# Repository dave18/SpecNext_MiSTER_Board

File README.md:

# SpecNext_MiSTER_Board
An extension board to provide Spectrum Next functionality to MiSTER

A MiSTer hat board MiSTER based on the offical schematics to (hopefully) allow better compatibility with the Spectrum Next core, including future updates.

It adds
* SRAM - up to 2 MB as per the next using 4 x as7c34096a-10 
* VGA out (using same resistor values from Next schematic)
* Mic/Ear port
* Audio out
* Two DB9 joystick ports
* NMI/Drive/Reset buttons
* J13 header to add physical SD Card support

Core code is based on the official MiSTer Spectrum Next Core with the following changes
* Direct VGA option - will bypass MiSTer framework and send direct video signal to VGA out (note - once this option is selected the OSD will no longer be visible over VGA until option is disabled (OSD is still visible through HDMI/DVI)
* Option to set each joystick to either MiSTer input or directly from the DSub 9 inputs
* Tape loading will automatically switch between virtual tape if loaded or from the Ear port if not
* SD Card interface will use virtual cards if loaded, else will use the J13 signals (useful if you have an Active Consult drive to plug in)

Changelog

Board V1.0 (Eagle files V3a)

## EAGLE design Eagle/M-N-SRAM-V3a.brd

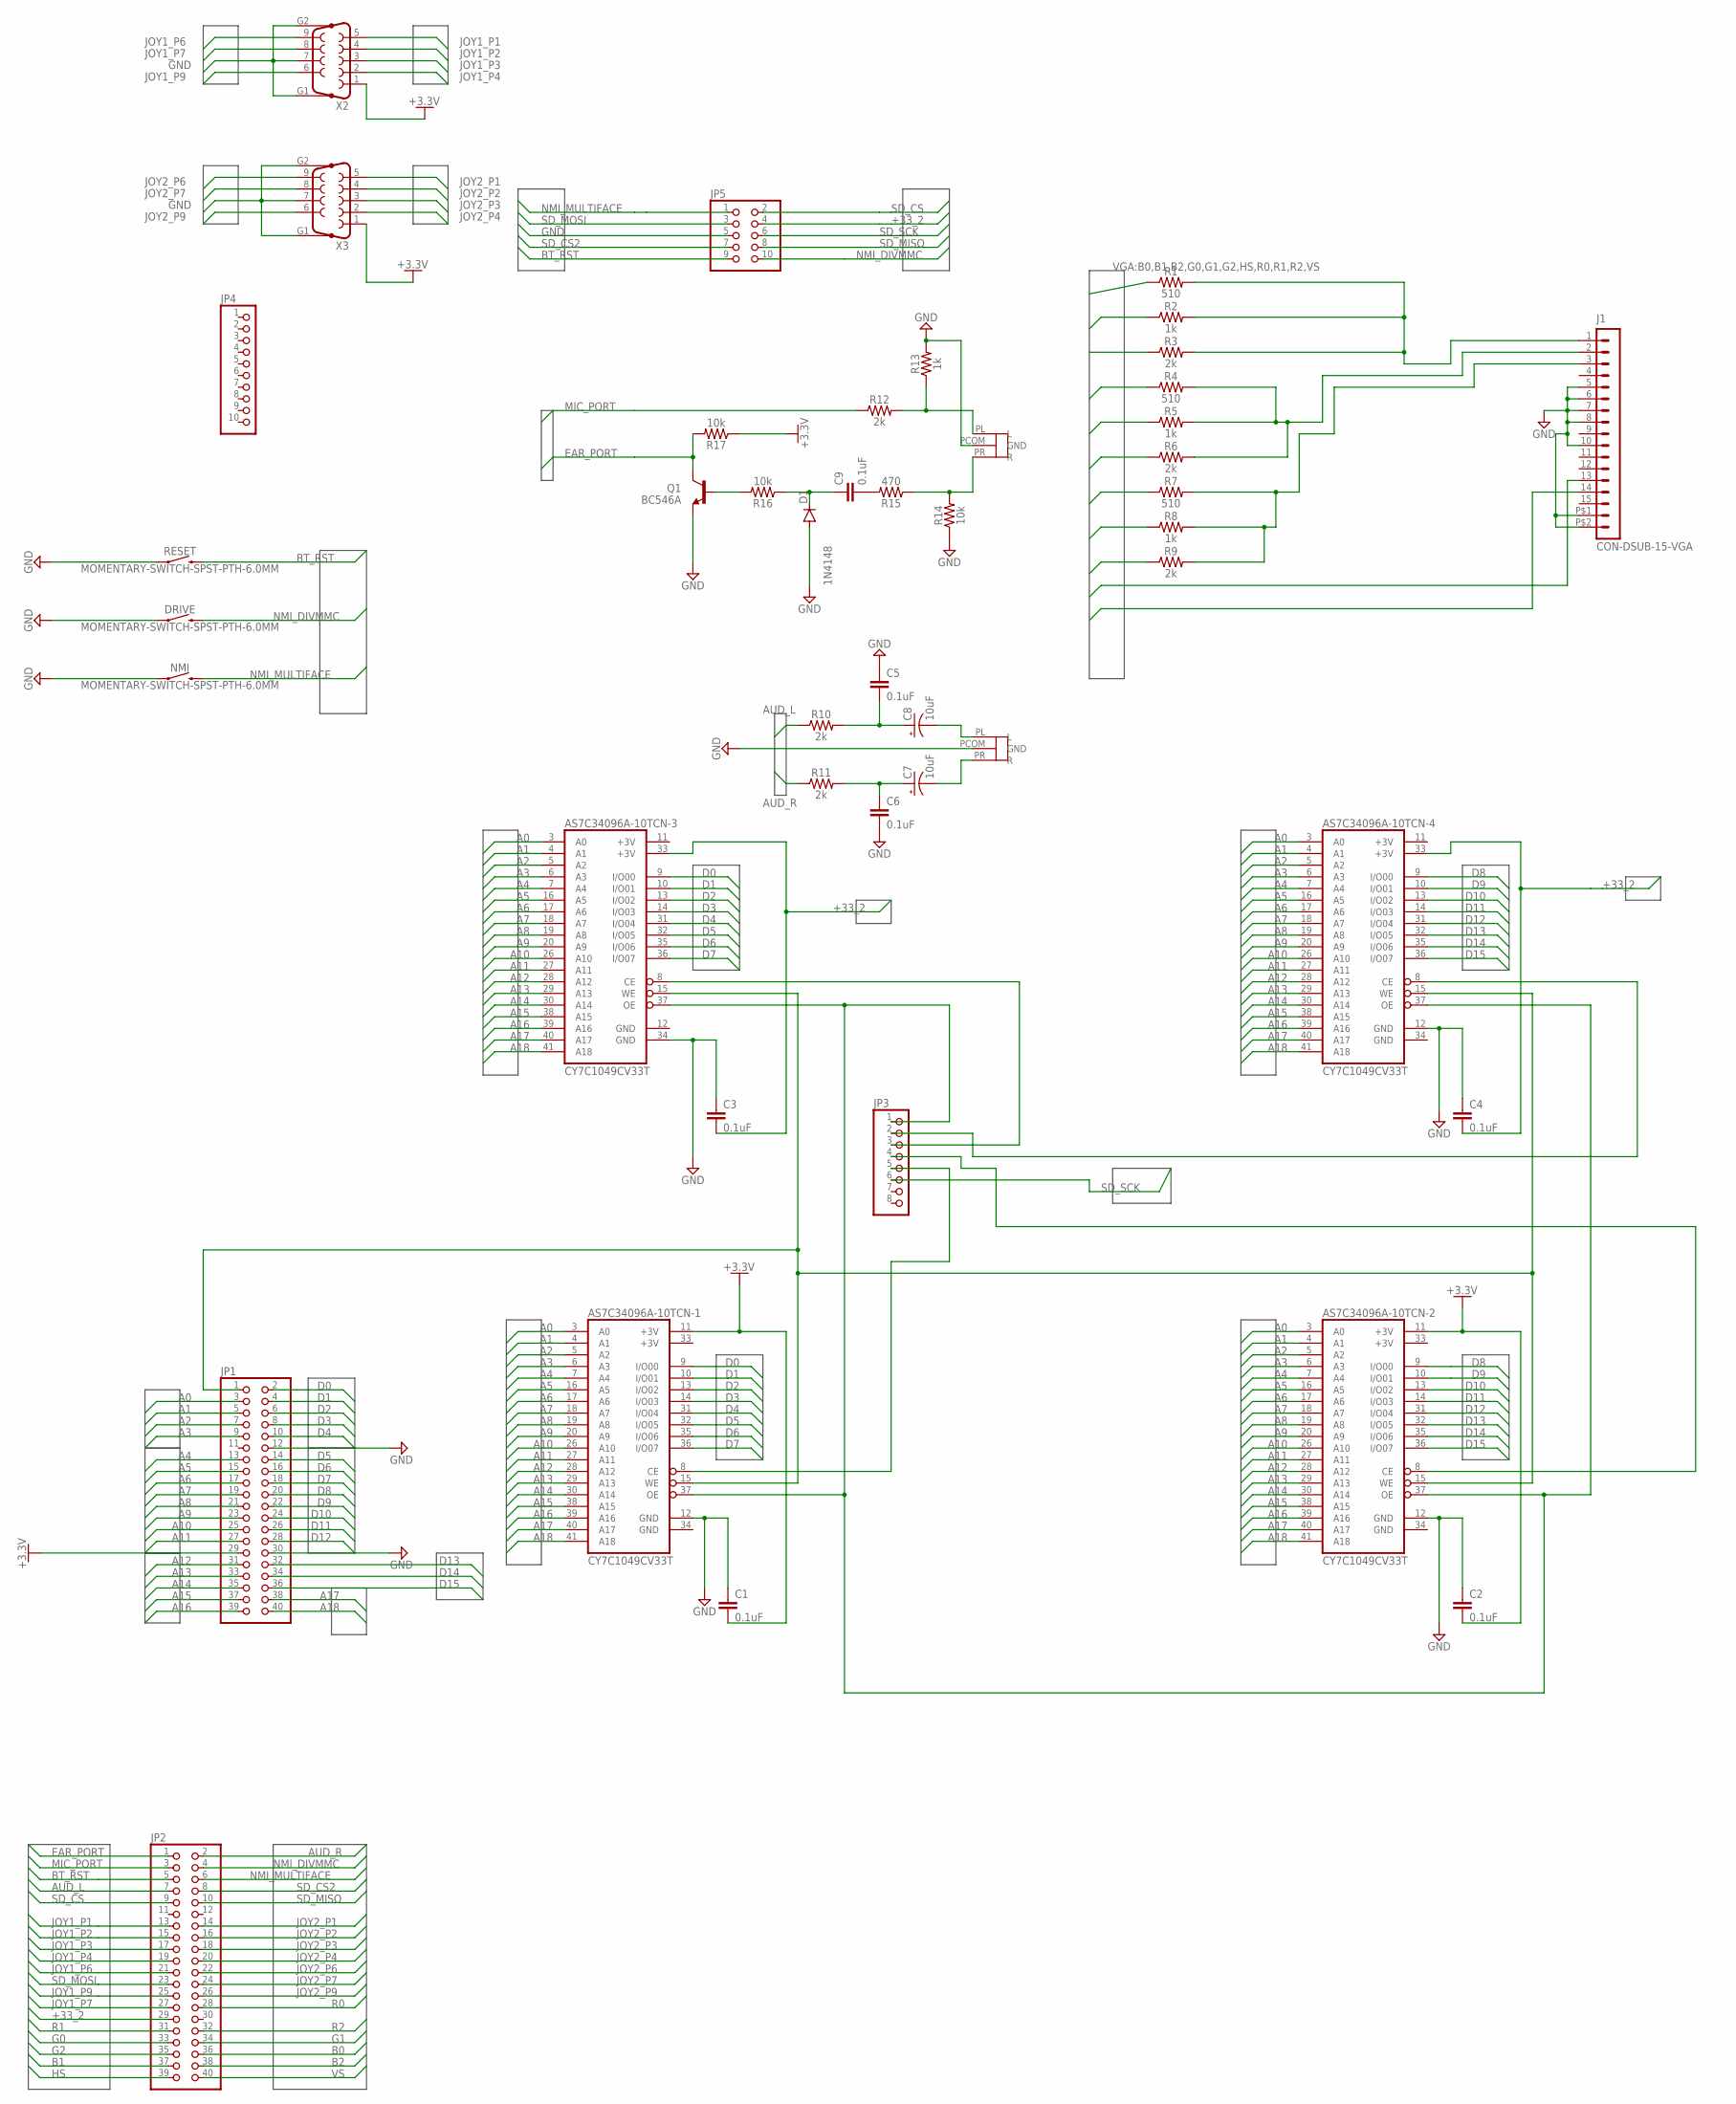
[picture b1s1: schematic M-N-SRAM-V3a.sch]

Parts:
AS7C34096A-10TCN-1, AS7C34096A-10TCN-2, AS7C34096A-10TCN-3, AS7C34096A-10TCN-4: CY7C1049CV33T; TSOPII-Z44
AUDIOOUT: AUDIOJACK
C1, C2, C3, C4, C5, C6, C9: 0.1uF; CAP-PTH-SMALL-KIT
C7, C8: 10uF; CPOL-RADIAL-2.5MM-5MM
D1: 1N4148; DO35-7
DRIVE: MOMENTARY-SWITCH-SPST-PTH-6.0MM; TACTILE_SWITCH_PTH_6.0MM
EAR/MIC: AUDIOJACK
J1: CON-DSUB-15-VGA; 181-015-212-171
JP1, JP2: PINHD-2X20; 2X20
JP3: PINHD-1X8; 1X08
JP4: PINHD-1X10; 1X10
JP5: PINHD-2X5; 2X05
NMI: MOMENTARY-SWITCH-SPST-PTH-6.0MM; TACTILE_SWITCH_PTH_6.0MM
Q1: BC546A; TO92-EBC
R1, R4, R7: 510; AXIAL-0.3
R2, R5, R8, R13: 1k; AXIAL-0.3
R3, R6, R9, R10, R11, R12: 2k; AXIAL-0.3
R14, R16, R17: 10k; AXIAL-0.3
R15: 470; AXIAL-0.3
RESET: MOMENTARY-SWITCH-SPST-PTH-6.0MM; TACTILE_SWITCH_PTH_6.0MM
X2, X3: F09HP

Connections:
+3.3V: AS7C34096A-10TCN-1.11 (+3V), AS7C34096A-10TCN-2.11 (+3V), C1.2, C2.2, R17.P$1 (1), X2.1, X3.1
+3V: AS7C34096A-10TCN-1.33 (+3V), AS7C34096A-10TCN-2.33 (+3V), AS7C34096A-10TCN-3.11 (+3V), AS7C34096A-10TCN-4.11 (+3V), JP1.29
+33_2: AS7C34096A-10TCN-3.33 (+3V), AS7C34096A-10TCN-4.33 (+3V), C3.2, C4.2, JP2.29, JP5.4
A0: AS7C34096A-10TCN-1.3 (A0), AS7C34096A-10TCN-2.3 (A0), AS7C34096A-10TCN-3.3 (A0), AS7C34096A-10TCN-4.3 (A0), JP1.3
A1: AS7C34096A-10TCN-1.4 (A1), AS7C34096A-10TCN-2.4 (A1), AS7C34096A-10TCN-3.4 (A1), AS7C34096A-10TCN-4.4 (A1), JP1.5
A2: AS7C34096A-10TCN-1.5 (A2), AS7C34096A-10TCN-2.5 (A2), AS7C34096A-10TCN-3.5 (A2), AS7C34096A-10TCN-4.5 (A2), JP1.7
A3: AS7C34096A-10TCN-1.6 (A3), AS7C34096A-10TCN-2.6 (A3), AS7C34096A-10TCN-3.6 (A3), AS7C34096A-10TCN-4.6 (A3), JP1.9
A4: AS7C34096A-10TCN-1.7 (A4), AS7C34096A-10TCN-2.7 (A4), AS7C34096A-10TCN-3.7 (A4), AS7C34096A-10TCN-4.7 (A4), JP1.13
A5: AS7C34096A-10TCN-1.16 (A5), AS7C34096A-10TCN-2.16 (A5), AS7C34096A-10TCN-3.16 (A5), AS7C34096A-10TCN-4.16 (A5), JP1.15
A6: AS7C34096A-10TCN-1.17 (A6), AS7C34096A-10TCN-2.17 (A6), AS7C34096A-10TCN-3.17 (A6), AS7C34096A-10TCN-4.17 (A6), JP1.17
A7: AS7C34096A-10TCN-1.18 (A7), AS7C34096A-10TCN-2.18 (A7), AS7C34096A-10TCN-3.18 (A7), AS7C34096A-10TCN-4.18 (A7), JP1.19
A8: AS7C34096A-10TCN-1.19 (A8), AS7C34096A-10TCN-2.19 (A8), AS7C34096A-10TCN-3.19 (A8), AS7C34096A-10TCN-4.19 (A8), JP1.21
A9: AS7C34096A-10TCN-1.20 (A9), AS7C34096A-10TCN-2.20 (A9), AS7C34096A-10TCN-3.20 (A9), AS7C34096A-10TCN-4.20 (A9), JP1.23
A10: AS7C34096A-10TCN-1.26 (A10), AS7C34096A-10TCN-2.26 (A10), AS7C34096A-10TCN-3.26 (A10), AS7C34096A-10TCN-4.26 (A10), JP1.25
A11: AS7C34096A-10TCN-1.27 (A11), AS7C34096A-10TCN-2.27 (A11), AS7C34096A-10TCN-3.27 (A11), AS7C34096A-10TCN-4.27 (A11), JP1.27
A12: AS7C34096A-10TCN-1.28 (A12), AS7C34096A-10TCN-2.28 (A12), AS7C34096A-10TCN-3.28 (A12), AS7C34096A-10TCN-4.28 (A12), JP1.31
A13: AS7C34096A-10TCN-1.29 (A13), AS7C34096A-10TCN-2.29 (A13), AS7C34096A-10TCN-3.29 (A13), AS7C34096A-10TCN-4.29 (A13), JP1.33
A14: AS7C34096A-10TCN-1.30 (A14), AS7C34096A-10TCN-2.30 (A14), AS7C34096A-10TCN-3.30 (A14), AS7C34096A-10TCN-4.30 (A14), JP1.35
A15: AS7C34096A-10TCN-1.38 (A15), AS7C34096A-10TCN-2.38 (A15), AS7C34096A-10TCN-3.38 (A15), AS7C34096A-10TCN-4.38 (A15), JP1.37
A16: AS7C34096A-10TCN-1.39 (A16), AS7C34096A-10TCN-2.39 (A16), AS7C34096A-10TCN-3.39 (A16), AS7C34096A-10TCN-4.39 (A16), JP1.39
A17: AS7C34096A-10TCN-1.40 (A17), AS7C34096A-10TCN-2.40 (A17), AS7C34096A-10TCN-3.40 (A17), AS7C34096A-10TCN-4.40 (A17), JP1.38
A18: AS7C34096A-10TCN-1.41 (A18), AS7C34096A-10TCN-2.41 (A18), AS7C34096A-10TCN-3.41 (A18), AS7C34096A-10TCN-4.41 (A18), JP1.40
AUDIO_OUT_L: AUDIOOUT.PL (L), C8.2 (-)
AUDIO_OUT_L1: C5.2, C8.1 (+), R10.P$2 (2)
AUDIO_OUT_R: AUDIOOUT.PR (R), C7.2 (-)
AUDIO_OUT_R1: C6.1, C7.1 (+), R11.P$2 (2)
AUD_L: JP2.7, R10.P$1 (1)
AUD_R: JP2.2, R11.P$1 (1)
B0: JP2.36, R7.P$1 (1)
B1: JP2.37, R8.P$1 (1)
B2: JP2.38, R9.P$1 (1)
BT_RST: JP2.5, JP5.9, RESET.3 (2)
D0: AS7C34096A-10TCN-1.9 (I/O00), AS7C34096A-10TCN-3.9 (I/O00), JP1.2
D1: AS7C34096A-10TCN-1.10 (I/O01), AS7C34096A-10TCN-3.10 (I/O01), JP1.4
D2: AS7C34096A-10TCN-1.13 (I/O02), AS7C34096A-10TCN-3.13 (I/O02), JP1.6
D3: AS7C34096A-10TCN-1.14 (I/O03), AS7C34096A-10TCN-3.14 (I/O03), JP1.8
D4: AS7C34096A-10TCN-1.31 (I/O04), AS7C34096A-10TCN-3.31 (I/O04), JP1.10
D5: AS7C34096A-10TCN-1.32 (I/O05), AS7C34096A-10TCN-3.32 (I/O05), JP1.14
D6: AS7C34096A-10TCN-1.35 (I/O06), AS7C34096A-10TCN-3.35 (I/O06), JP1.16
D7: AS7C34096A-10TCN-1.36 (I/O07), AS7C34096A-10TCN-3.36 (I/O07), JP1.18
D8: AS7C34096A-10TCN-2.9 (I/O00), AS7C34096A-10TCN-4.9 (I/O00), JP1.20
D9: AS7C34096A-10TCN-2.10 (I/O01), AS7C34096A-10TCN-4.10 (I/O01), JP1.22
D10: AS7C34096A-10TCN-2.13 (I/O02), AS7C34096A-10TCN-4.13 (I/O02), JP1.24
D11: AS7C34096A-10TCN-2.14 (I/O03), AS7C34096A-10TCN-4.14 (I/O03), JP1.26
D12: AS7C34096A-10TCN-2.31 (I/O04), AS7C34096A-10TCN-4.31 (I/O04), JP1.28
D13: AS7C34096A-10TCN-2.32 (I/O05), AS7C34096A-10TCN-4.32 (I/O05), JP1.32
D14: AS7C34096A-10TCN-2.35 (I/O06), AS7C34096A-10TCN-4.35 (I/O06), JP1.34
D15: AS7C34096A-10TCN-2.36 (I/O07), AS7C34096A-10TCN-4.36 (I/O07), JP1.36
EAR_PORT: JP2.1, Q1.C, R17.P$2 (2)
G0: JP2.33, R4.P$1 (1)
G1: JP2.34, R5.P$1 (1)
G2: JP2.35, R6.P$1 (1)
GND: AS7C34096A-10TCN-1.12 (GND), AS7C34096A-10TCN-1.34 (GND), AS7C34096A-10TCN-2.12 (GND), AS7C34096A-10TCN-2.34 (GND), AS7C34096A-10TCN-3.12 (GND), AS7C34096A-10TCN-3.34 (GND), AS7C34096A-10TCN-4.12 (GND), AS7C34096A-10TCN-4.34 (GND), AUDIOOUT.PCOM (GND), C1.1, C2.1, C3.1, C4.1, C5.1, C6.2, D1.A, DRIVE.1, EAR/MIC.PCOM (GND), J1.5, J1.6, J1.7, J1.8, J1.10, J1.P$1 (16), J1.P$2 (17), JP1.12, JP1.30, JP5.5, NMI.1, Q1.E, R13.P$2 (2), R14.P$1 (1), RESET.1, X2.7, X2.G1, X2.G2, X3.7, X3.G1, X3.G2
HS: J1.13, JP2.39
JOY1_P1: JP2.13, X2.5
JOY1_P2: JP2.15, X2.4
JOY1_P3: JP2.17, X2.3
JOY1_P4: JP2.19, X2.2
JOY1_P6: JP2.21, X2.9
JOY1_P7: JP2.27, X2.8
JOY1_P9: JP2.25, X2.6
JOY2_P1: JP2.14, X3.5
JOY2_P2: JP2.16, X3.4
JOY2_P3: JP2.18, X3.3
JOY2_P4: JP2.20, X3.2
JOY2_P6: JP2.22, X3.9
JOY2_P7: JP2.24, X3.8
JOY2_P9: JP2.26, X3.6
MIC_PORT: JP2.3, R12.P$1 (1)
unnamed: EAR/MIC.PL (L), R12.P$2 (2), R13.P$1 (1)
unnamed: C9.2, R15.P$2 (2)
unnamed: EAR/MIC.PR (R), R14.P$2 (2), R15.P$1 (1)
unnamed: C9.1, D1.C, R16.P$1 (1)
unnamed: Q1.B, R16.P$2 (2)
NMI_DIVMMC: DRIVE.3 (2), JP2.4, JP5.10
NMI_MULTIFACE: JP2.6, JP5.1, NMI.3 (2)
R0: JP2.28, R1.P$1 (1)
R1: JP2.31, R2.P$1 (1)
R2: JP2.32, R3.P$1 (1)
RAM_CE1: AS7C34096A-10TCN-1.8 (CE), JP3.5
RAM_CE2: AS7C34096A-10TCN-2.8 (CE), JP3.4
RAM_CE3: AS7C34096A-10TCN-3.8 (CE), JP3.3
RAM_CE4: AS7C34096A-10TCN-4.8 (CE), JP3.2
RAM_OE: AS7C34096A-10TCN-1.37 (OE), AS7C34096A-10TCN-2.37 (OE), AS7C34096A-10TCN-3.37 (OE), AS7C34096A-10TCN-4.37 (OE), JP3.1
RAM_WE: AS7C34096A-10TCN-1.15 (WE), AS7C34096A-10TCN-2.15 (WE), AS7C34096A-10TCN-3.15 (WE), AS7C34096A-10TCN-4.15 (WE), JP1.1
SD_CS: JP2.9, JP5.2
SD_CS2: JP2.8, JP5.7
SD_MISO: JP2.10, JP5.8
SD_MOSI: JP2.23, JP5.3
SD_SCK: JP3.6, JP5.6
VGA_BLUE: J1.3, R7.P$2 (2), R8.P$2 (2), R9.P$2 (2)
VGA_GREEN: J1.2, R4.P$2 (2), R5.P$2 (2), R6.P$2 (2)
VGA_RED: J1.1, R1.P$2 (2), R2.P$2 (2), R3.P$2 (2)
VS: J1.14, JP2.40

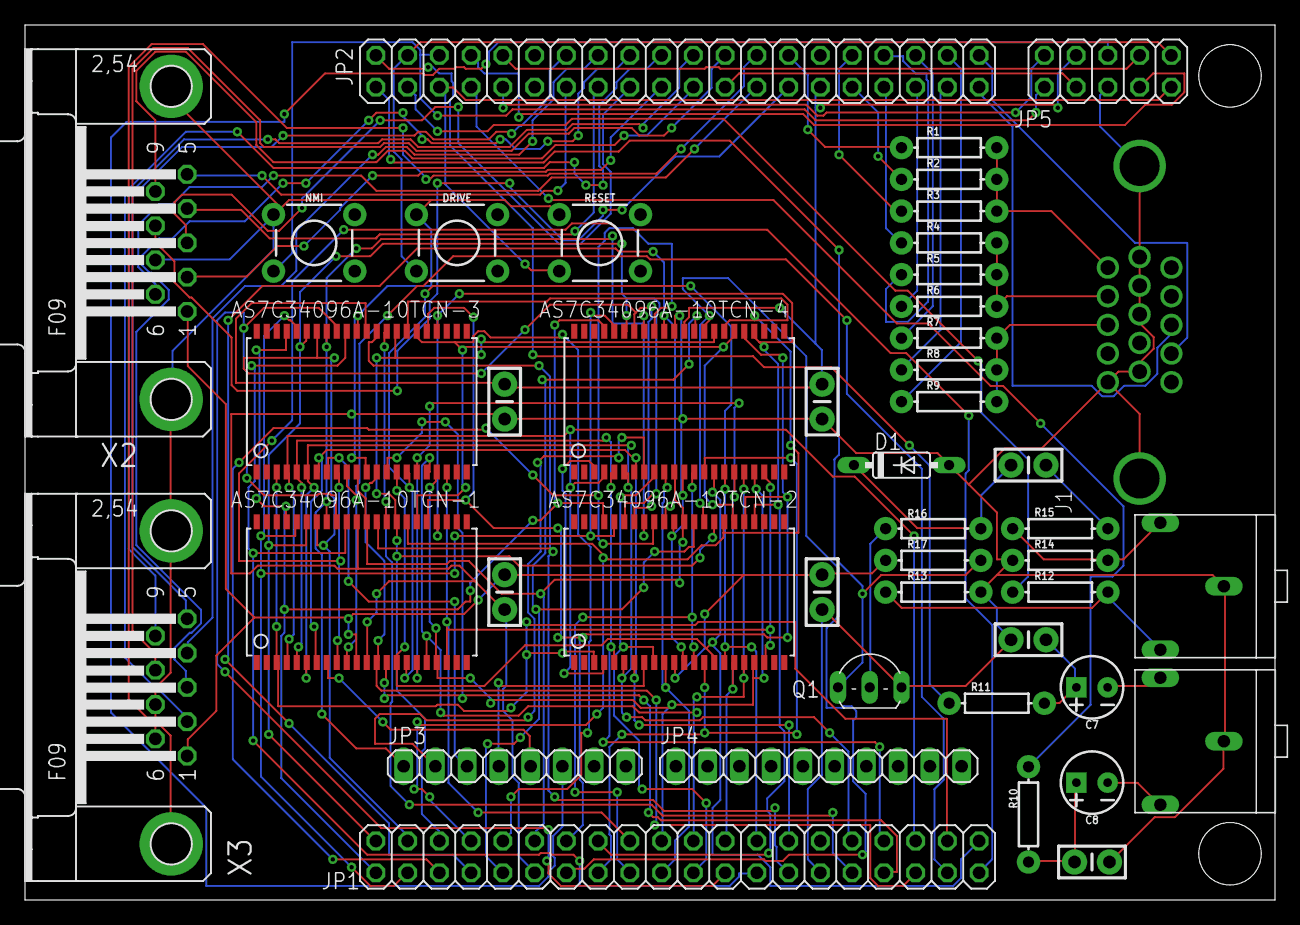
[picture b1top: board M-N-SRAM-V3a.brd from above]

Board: 2 copper layers, 100.0 x 70.0 mm, 45 parts (0 on the bottom side), 94 nets.

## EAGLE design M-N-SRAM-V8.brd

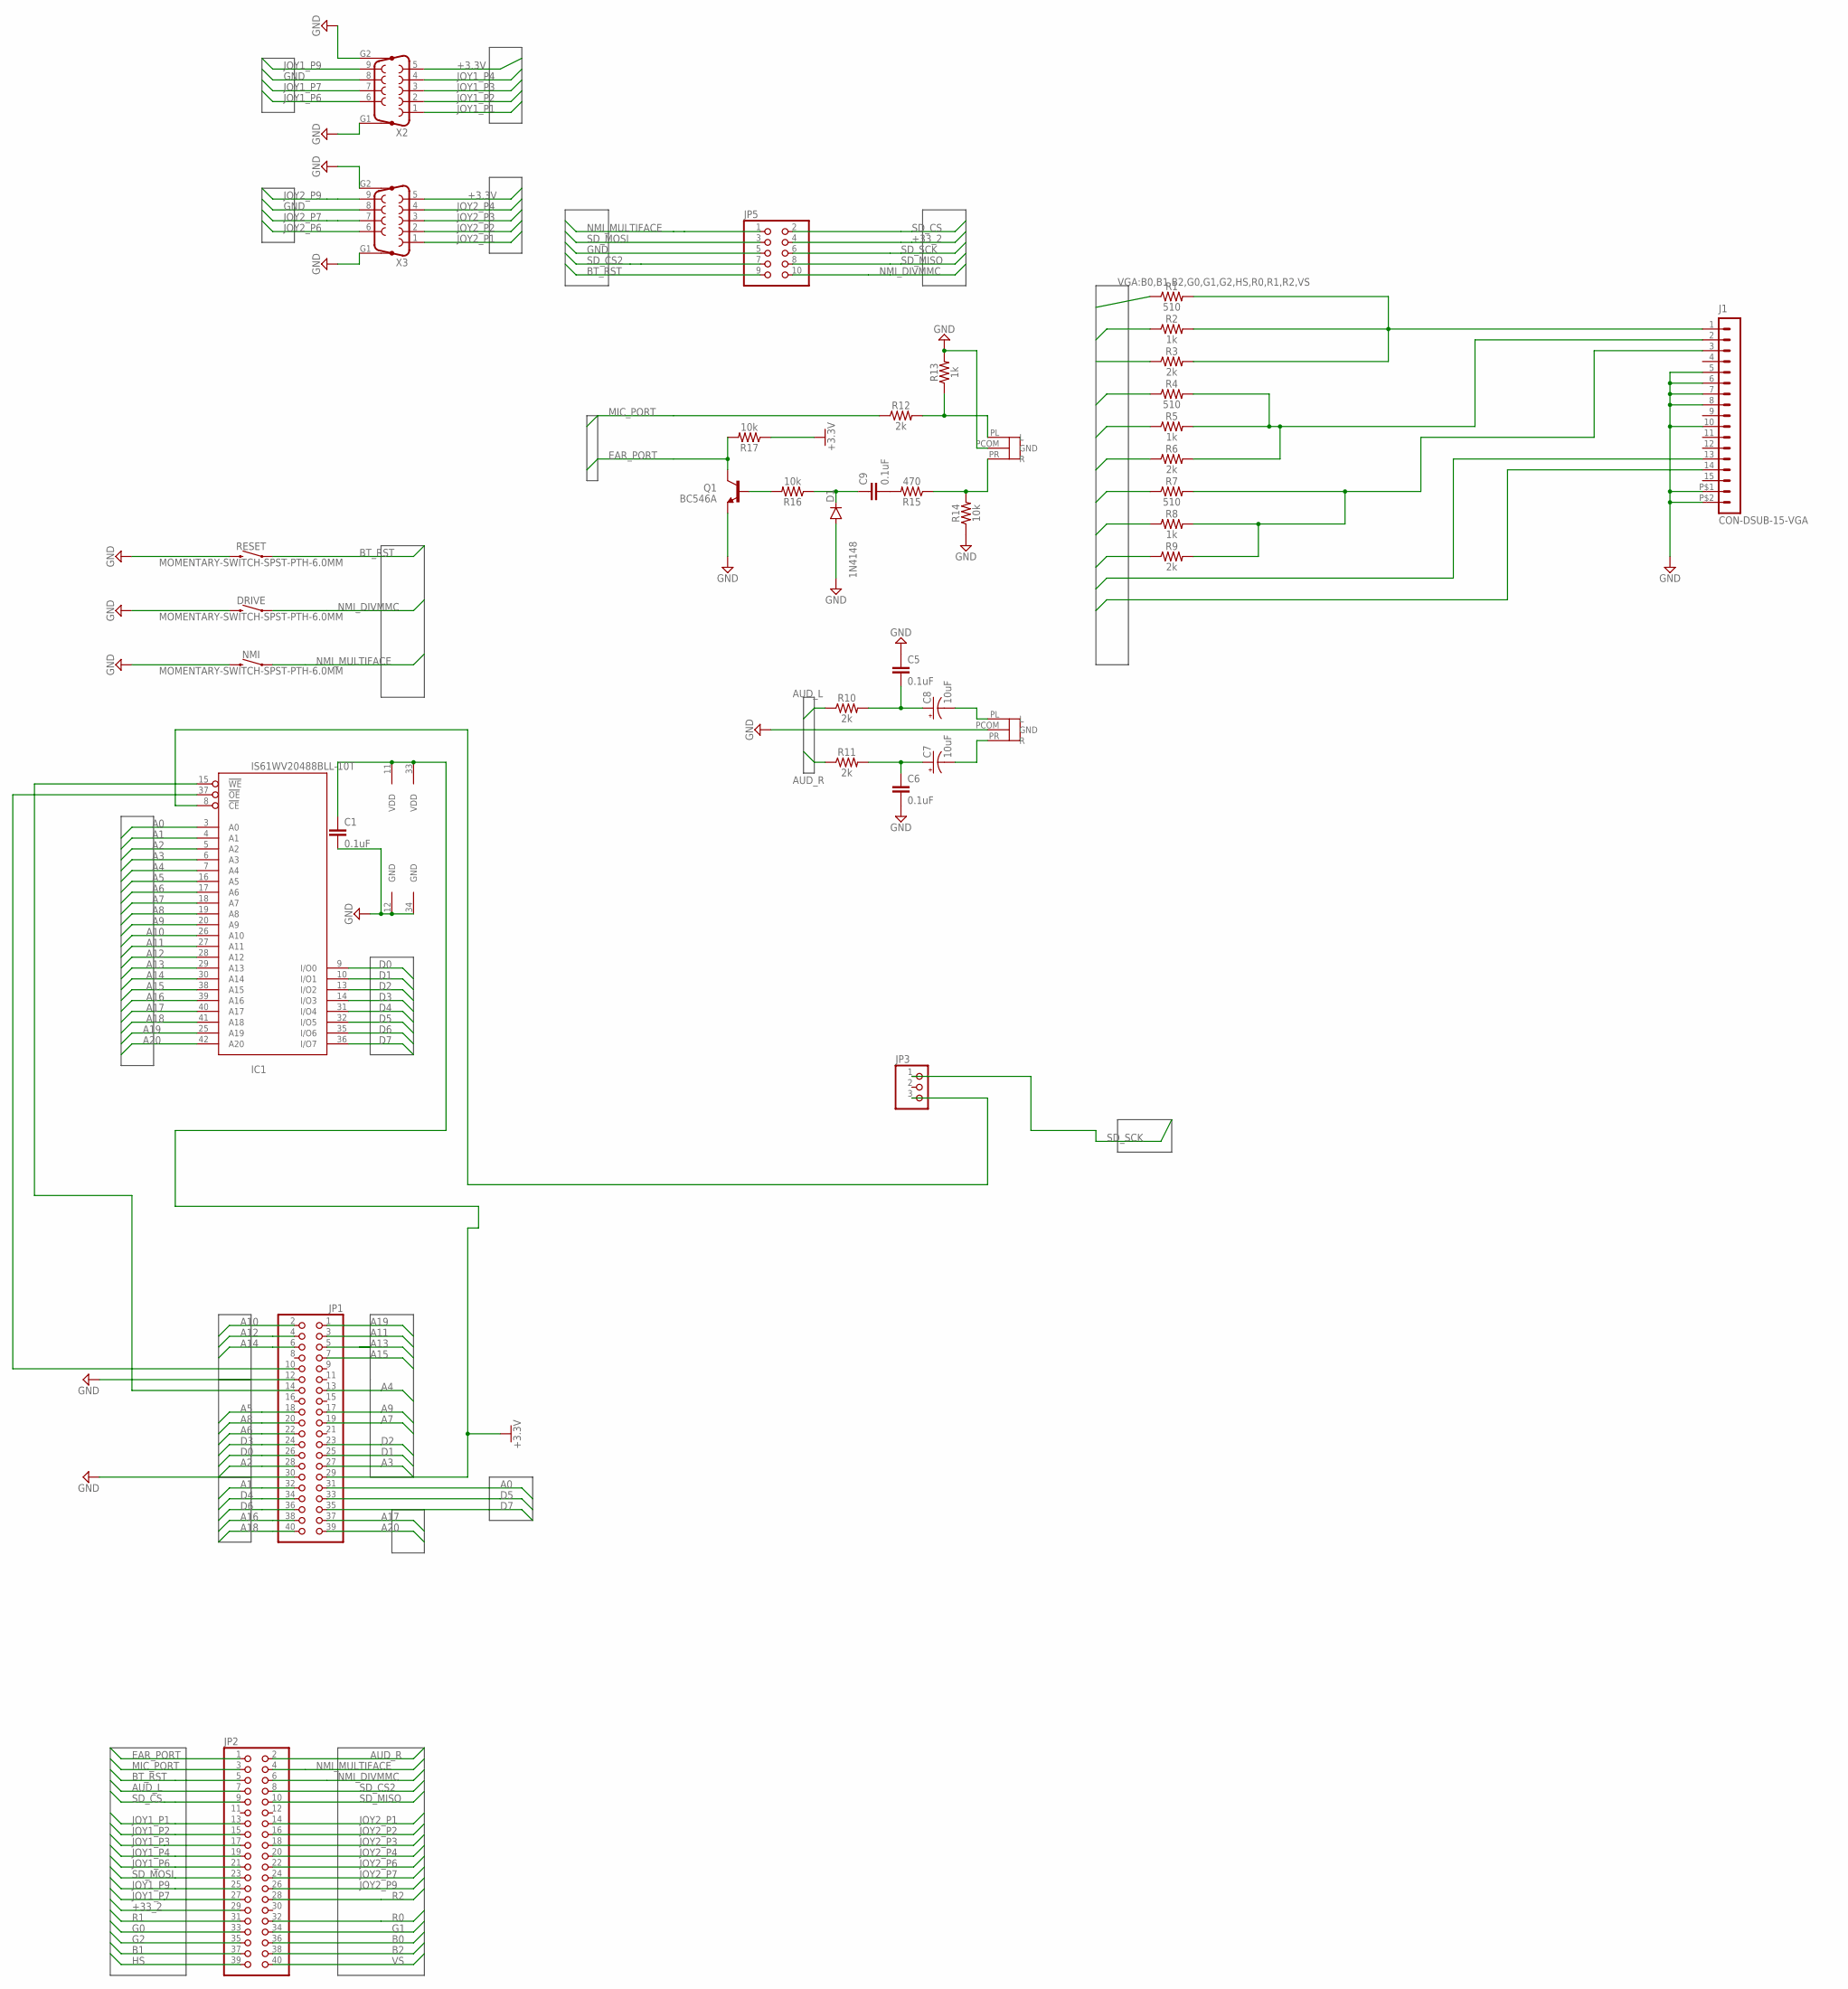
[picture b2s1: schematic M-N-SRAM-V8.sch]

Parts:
AUDIOOUT: AUDIOJACK
C1, C5, C6, C9: 0.1uF; CAP-PTH-SMALL-KIT
C7, C8: 10uF; CPOL-RADIAL-2.5MM-5MM
D1: 1N4148; DO35-7
DRIVE: MOMENTARY-SWITCH-SPST-PTH-6.0MM; TACTILE_SWITCH_PTH_6.0MM
EAR/MIC: AUDIOJACK
IC1: IS61WV20488BLL-10T; TSOP-II-44
J1: CON-DSUB-15-VGA; 181-015-212-171
JP1, JP2: PINHD-2X20; 2X20
JP3: PINHD-1X3; 1X03
JP5: PINHD-2X5; 2X05
NMI: MOMENTARY-SWITCH-SPST-PTH-6.0MM; TACTILE_SWITCH_PTH_6.0MM
Q1: BC546A; TO92-EBC
R1, R4, R7: 510; AXIAL-0.3
R2, R5, R8, R13: 1k; AXIAL-0.3
R3, R6, R9, R10, R11, R12: 2k; AXIAL-0.3
R14, R16, R17: 10k; AXIAL-0.3
R15: 470; AXIAL-0.3
RESET: MOMENTARY-SWITCH-SPST-PTH-6.0MM; TACTILE_SWITCH_PTH_6.0MM
X2, X3: F09HP

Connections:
+3.3V: C1.1, IC1.11 (VDD), IC1.33 (VDD), JP1.29, R17.P$1 (1), X2.5, X3.5
+33_2: JP2.29, JP5.4
A0: IC1.3 (A0), JP1.31
A1: IC1.4 (A1), JP1.32
A2: IC1.5 (A2), JP1.28
A3: IC1.6 (A3), JP1.27
A4: IC1.7 (A4), JP1.13
A5: IC1.16 (A5), JP1.18
A6: IC1.17 (A6), JP1.22
A7: IC1.18 (A7), JP1.19
A8: IC1.19 (A8), JP1.20
A9: IC1.20 (A9), JP1.17
A10: IC1.26 (A10), JP1.2
A11: IC1.27 (A11), JP1.3
A12: IC1.28 (A12), JP1.4
A13: IC1.29 (A13), JP1.5
A14: IC1.30 (A14), JP1.6
A15: IC1.38 (A15), JP1.7
A16: IC1.39 (A16), JP1.38
A17: IC1.40 (A17), JP1.37
A18: IC1.41 (A18), JP1.40
A19: IC1.25 (A19), JP1.1
A20: IC1.42 (A20), JP1.39
AUDIO_OUT_L: AUDIOOUT.PL (L), C8.2 (-)
AUDIO_OUT_L1: C5.2, C8.1 (+), R10.P$2 (2)
AUDIO_OUT_R: AUDIOOUT.PR (R), C7.2 (-)
AUDIO_OUT_R1: C6.1, C7.1 (+), R11.P$2 (2)
AUD_L: JP2.7, R10.P$1 (1)
AUD_R: JP2.2, R11.P$1 (1)
B0: JP2.36, R7.P$1 (1)
B1: JP2.37, R8.P$1 (1)
B2: JP2.38, R9.P$1 (1)
BT_RST: JP2.5, JP5.9, RESET.1
D0: IC1.9 (I/O0), JP1.26
D1: IC1.10 (I/O1), JP1.25
D2: IC1.13 (I/O2), JP1.23
D3: IC1.14 (I/O3), JP1.24
D4: IC1.31 (I/O4), JP1.34
D5: IC1.32 (I/O5), JP1.33
D6: IC1.35 (I/O6), JP1.36
D7: IC1.36 (I/O7), JP1.35
EAR_PORT: JP2.1, Q1.C, R17.P$2 (2)
G0: JP2.33, R4.P$1 (1)
G1: JP2.34, R5.P$1 (1)
G2: JP2.35, R6.P$1 (1)
GND: AUDIOOUT.PCOM (GND), C1.2, C5.1, C6.2, D1.A, DRIVE.3 (2), EAR/MIC.PCOM (GND), IC1.12 (GND), IC1.34 (GND), J1.5, J1.6, J1.7, J1.8, J1.10, J1.P$1 (16), J1.P$2 (17), JP1.12, JP1.30, JP5.5, NMI.3 (2), Q1.E, R13.P$2 (2), R14.P$1 (1), RESET.3 (2), X2.8, X2.G1, X2.G2, X3.8, X3.G1, X3.G2
HS: J1.13, JP2.39
JOY1_P1: JP2.13, X2.1
JOY1_P2: JP2.15, X2.2
JOY1_P3: JP2.17, X2.3
JOY1_P4: JP2.19, X2.4
JOY1_P6: JP2.21, X2.6
JOY1_P7: JP2.27, X2.7
JOY1_P9: JP2.25, X2.9
JOY2_P1: JP2.14, X3.1
JOY2_P2: JP2.16, X3.2
JOY2_P3: JP2.18, X3.3
JOY2_P4: JP2.20, X3.4
JOY2_P6: JP2.22, X3.6
JOY2_P7: JP2.24, X3.7
JOY2_P9: JP2.26, X3.9
MIC_PORT: JP2.3, R12.P$1 (1)
unnamed: EAR/MIC.PL (L), R12.P$2 (2), R13.P$1 (1)
unnamed: C9.2, R15.P$2 (2)
unnamed: EAR/MIC.PR (R), R14.P$2 (2), R15.P$1 (1)
unnamed: C9.1, D1.C, R16.P$1 (1)
unnamed: Q1.B, R16.P$2 (2)
NMI_DIVMMC: DRIVE.1, JP2.6, JP5.10
NMI_MULTIFACE: JP2.4, JP5.1, NMI.1
R0: JP2.32, R1.P$1 (1)
R1: JP2.31, R2.P$1 (1)
R2: JP2.28, R3.P$1 (1)
RAM_CE: IC1.8 (!CE), JP3.3
RAM_OE: IC1.37 (!OE), JP1.10
RAM_WE: IC1.15 (!WE), JP1.14
SD_CS: JP2.9, JP5.2
SD_CS2: JP2.8, JP5.7
SD_MISO: JP2.10, JP5.8
SD_MOSI: JP2.23, JP5.3
SD_SCK: JP3.1, JP5.6
VGA_BLUE: J1.3, R7.P$2 (2), R8.P$2 (2), R9.P$2 (2)
VGA_GREEN: J1.2, R4.P$2 (2), R5.P$2 (2), R6.P$2 (2)
VGA_RED: J1.1, R1.P$2 (2), R2.P$2 (2), R3.P$2 (2)
VS: J1.14, JP2.40

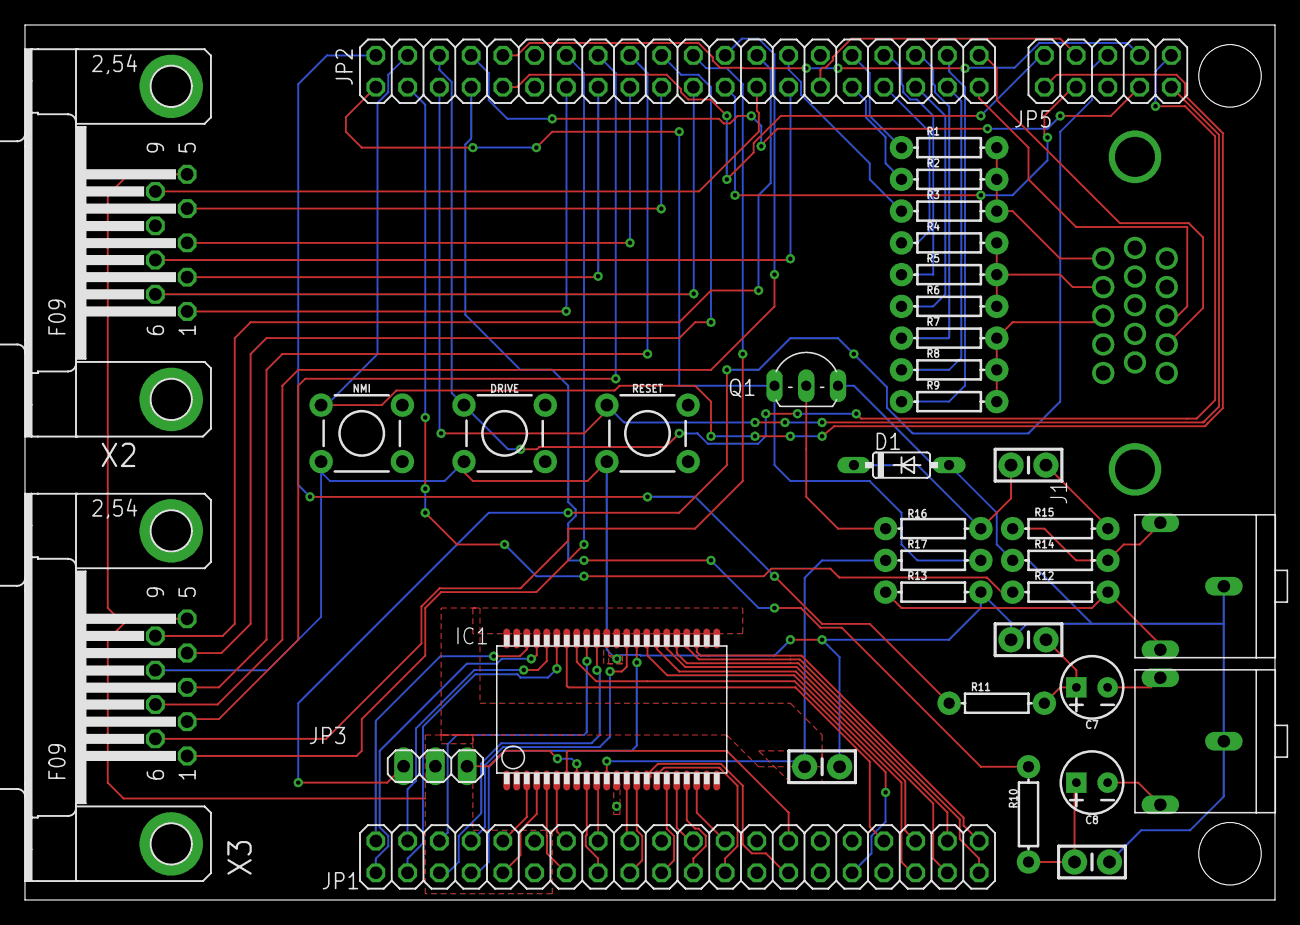
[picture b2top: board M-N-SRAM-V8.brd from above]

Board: 2 copper layers, 100.0 x 70.0 mm, 38 parts (0 on the bottom side), 84 nets.

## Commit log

2021-03-24 Rename images
2021-03-24 Add v8 Eagle files
    V8 Eagle files relate to official V2.0 board
2021-03-24 Schematic Correction
2022-01-31 Add files via upload
    Upload of Working CAM file

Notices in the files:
parts and their libraries:
SparkFun-Capacitors: Licensing: Creative Commons ShareAlike 4.0 International - https://creativecommons.org/licenses/by-sa/4.0
m-pad-2.1: License : GNU General Public License version 2 (see bottom)
